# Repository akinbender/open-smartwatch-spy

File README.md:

# Open-Smartwatch Spy Edition beta
Based on the open source smartwatch project [Open-Smartwatch](https://open-smartwatch.github.io/) by [Paul's 3D Things](https://www.instagram.com/pauls_3d_things/?hl=en).
The rugged box is designed after this thingiverse [project](https://www.thingiverse.com/thing:4094861)
Check out my twitter [thread](https://twitter.com/AlternatifAkin/status/1460656525509369863) about the build.

## Must TODOs for v1.0 release
1. Fix button placements. (Buttons are in wrong order)
2. add female connector for battery, soldering is really unpleasent at that point of the assembly.
3. buy some other micro stepper motor such as [this geared one](https://www.ebay.de/itm/193621782182?_trkparms=amclksrc%3DITM%26aid%3D111001%26algo%3DREC.SEED%26ao%3D1%26asc%3D20170511121231%26meid%3D0d5549f075dd4680823e29a32ba356f4%26pid%3D100675%26rk%3D8%26rkt%3D15%26sd%3D114305088477%26itm%3D193621782182%26pmt%3D1%26noa%3D1%26pg%3D2380057%26brand%3DUnbranded&_trksid=p2380057.c100675.m4236&_trkparms=pageci%3A7b14f08c-a37a-11ec-b54c-b2d4c27de75e%7Cparentrq%3A87caf1d717f0ab9e8780c580fffe10da%7Ciid%3A1) and a female [connector](https://www.aliexpress.com/item/4000012574440.html?spm=a2g0o.productlist.0.0.6e081f6dXTVHuh&algo_pvid=905ba21a-fd4a-4362-94af-929b954b7658&algo_exp_id=905ba21a-fd4a-4362-94af-929b954b7658-18&pdp_ext_f=%7B%22sku_id%22%3A%2210000000031868706%22%7D&pdp_pi=-1%3B1.22%3B-1%3B-1%40salePrice%3BEUR%3Bsearch-mainSearch) for it.
4. find schematic and footprint of the afformentioned female connector for the board, and order new pcb.
5. 3d design of the new motor & release mechanism
6. finish osw firmware extension for motor control (didn't check it in, not required at this point)
7. Fix rugged box design. (Current design cannot fit the straps and only has two dart holders) Also gotta fix my 3d printer to print another one.. 

## Optional TODOs
Check out Paul's instagram page, he has designed an awesome new watch. Ultimately and hopefully, I will also switch to the new board design.  I dont know which changes are going to be included when, but I have some plans.

1. switch micro-USB for [waterproof 4 pin connector](https://www.aliexpress.com/item/1005003687986489.html?spm=a2g0o.productlist.0.0.41f07ac9adyMLZ&algo_pvid=9baeaac9-50b3-4902-a8c2-167efe2e5cce&aem_p4p_detail=20220314132643344794801503300032362813&algo_exp_id=9baeaac9-50b3-4902-a8c2-167efe2e5cce-0&pdp_ext_f=%7B%22sku_id%22%3A%2212000026806960583%22%7D&pdp_pi=-1%3B8.4%3B-1%3B6.29%40salePrice%3BEUR%3Bsearch-mainSearch)
2. switch buttons for some waterproof alternative, maybe seperate pcb touch buttons?
3. waterproof design with O-rings and stuff, don't really know how yet..
4. Induction Charging [option](https://www.aliexpress.com/item/1005003691851748.html?spm=a2g0o.productlist.0.0.fb831482BUJV1L&algo_pvid=5ddf7b3c-2e64-4216-bba5-416096ba6f9b&aem_p4p_detail=202203141410075793754545811920016464366&algo_exp_id=5ddf7b3c-2e64-4216-bba5-416096ba6f9b-0&pdp_ext_f=%7B%22sku_id%22%3A%2212000026821101659%22%7D&pdp_pi=-1%3B14.19%3B-1%3B1.81%40salePrice%3BEUR%3Bsearch-mainSearch) 

## Notes
Currently there is a fully plastic test dart, and one that can be fashioned out of a M3 allen key. Depending on multiple build desicions, you can really end up hurting someone with the metal dart. This should go without saying, but I (and Paul) obviously do not accept any responsibility, I never do..

Also going to visit a local magic shop for guidance about trick darts. Magic is all about deception, most spygear too.. So maybe I might build some pyro, flash or smoke darts. Can also build an injector dart. I looked closely to my Covid vaccine injector, it can fit inside the chamber but there is no way that it can be useful.

###### I named the project because well, it's obvious right? But my aim was to build a self protection gear in the form of a daily wearable item for my sis and my mom. And lets face it, shooting darts is not the optimal solution for them. Long story short, after v1.0 release an alternative design with a gas canister instead of a dart shooter is also needed.

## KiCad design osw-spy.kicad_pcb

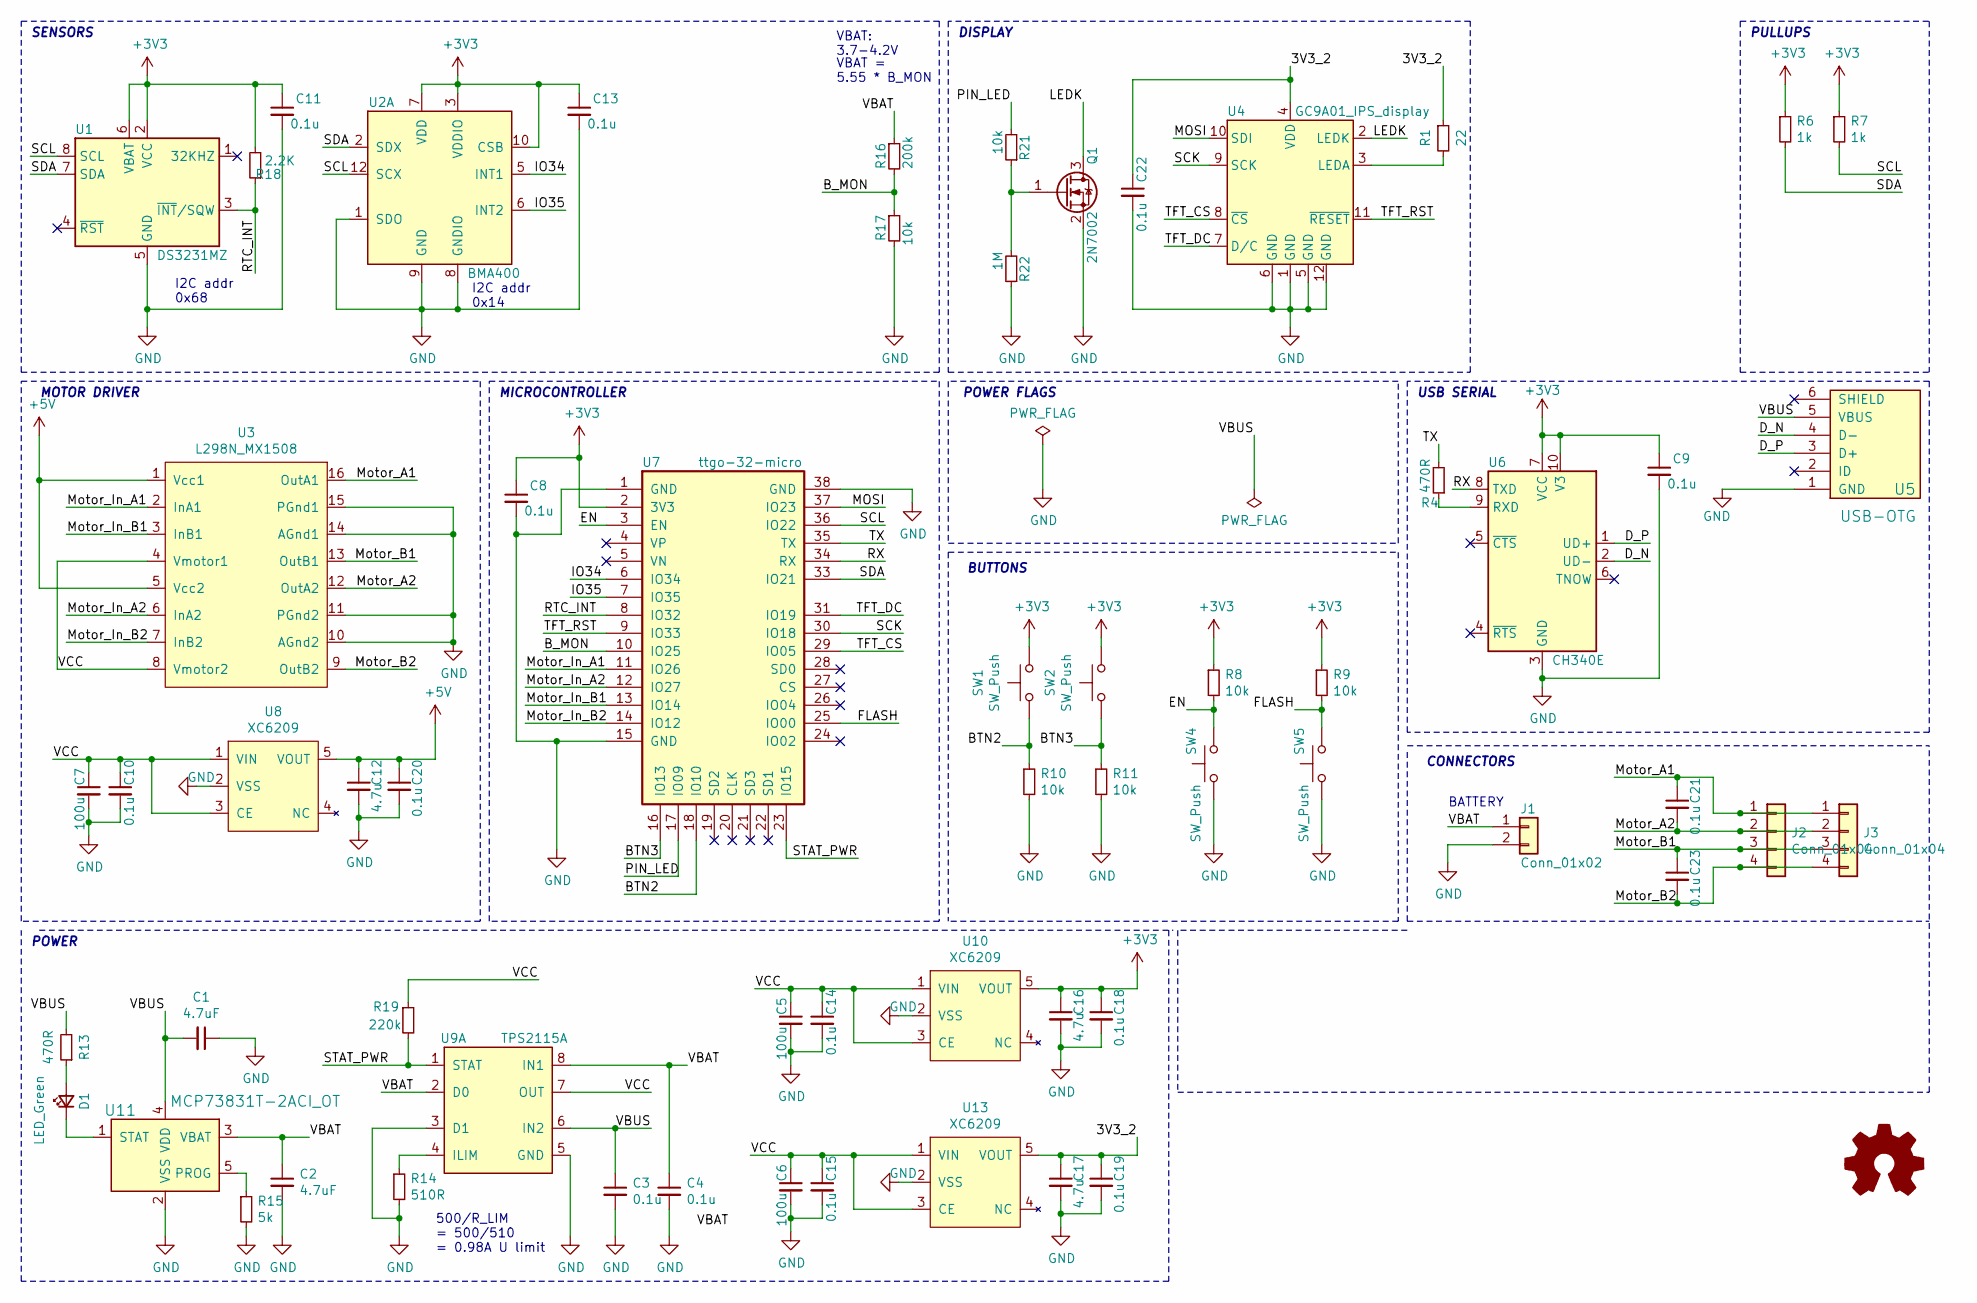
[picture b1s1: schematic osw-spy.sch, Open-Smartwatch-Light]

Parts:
C1, C2: 4.7uF; C_0603_1608Metric
C3, C4, C8, C9, C10, C11, C13, C14, C15, C18, C19, C20, C21, C22, C23: 0.1u; C_0603_1608Metric
C5, C6, C7: 100u; C_1206_3216Metric
C12, C16, C17: 4.7u; C_0603_1608Metric
D1: LED_Green; LED_0805_2012Metric
J1: Conn_01x02; PinHeader_1x02_P2.54mm_Vertical
J2, J3: Conn_01x04; PinHeader_1x04_P2.54mm_Vertical
Q1: 2N7002; SOT-23
R1: 22; R_0603_1608Metric
R4, R13: 470R; R_0603_1608Metric
R6, R7: 1k; R_0603_1608Metric
R8, R9, R10, R11, R17, R21: 10k; R_0603_1608Metric
R14: 510R; R_0603_1608Metric
R15: 5k; R_0603_1608Metric
R16: 200k; R_0603_1608Metric
R18: 2.2K; R_0603_1608Metric
R19: 220k; R_0603_1608Metric
R22: 1M; R_0603_1608Metric
SW1, SW2, SW4, SW5: SW_Push; button_side_smd
U1: DS3231MZ; SOIC-8_3.9x4.9mm_P1.27mm
U2: BMA400; LGA-12_2x2mm_P0.5mm; MPN BMA400; DigiKey_PN 828-1081-1-ND
U3: L298N_MX1508; SOP-16_3.9x9.9mm_P1.27mm
U4: GC9A01_IPS_display
U5: USB-OTG; USBmicro-B
U6: CH340E; MSOP-10_3x3mm_P0.5mm
U7: ttgo-32-micro
U8, U10, U13: XC6209; SOT-23-5
U9: TPS2115A; TSSOP-8_4.4x3mm_P0.65mm; MPN TPS2115APWR; DigiKey_PN 296-16940-1-ND
U11: MCP73831T-2ACI_OT; SOT-23-5; MPN MCP73831T-2ACI/OT; Digi-Key_PN MCP73831T-2ACI/OTCT-ND

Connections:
+3V3: C8.1, C9.1, C11.1, C13.1, C16.1, C18.1, R6.1, R7.1, R8.1, R9.1, R18.2, SW1.2, SW2.2, U1.2 (VCC), U1.6 (VBAT), U2.3 (VDDIO), U2.7 (VDD), U2.10 (CSB), U6.7 (VCC), U6.10 (V3), U7.2 (3V3), U10.5 (VOUT)
+5V: C12.1, C20.1, U3.1 (Vcc1), U3.5 (Vcc2), U8.5 (VOUT)
/3V3_2: C17.1, C19.1, C22.1, R1.1, U4.4 (VDD), U13.5 (VOUT)
/BTN2: R10.1, SW1.1, U7.18 (IO10)
/BTN3: R11.1, SW2.1, U7.16 (IO13)
/B_MON: R16.2, R17.1, U7.10 (IO25)
/D_N: U5.4 (D-), U6.2 (UD-)
/D_P: U5.3 (D+), U6.1 (UD+)
/EN: R8.2, SW4.2, U7.3 (EN)
/FLASH: R9.2, SW5.2, U7.25 (IO00)
/IO34: U2.5 (INT1), U7.6 (IO34)
/IO35: U2.6 (INT2), U7.7 (IO35)
/LEDK: Q1.3 (D), U4.2 (LEDK)
/MOSI: U4.10 (SDI), U7.37 (IO23)
/Motor_A1: C21.1, J2.1, J3.1, U3.16 (OutA1)
/Motor_A2: C21.2, J2.2, J3.2, U3.12 (OutA2)
/Motor_B1: C23.1, J2.3, J3.3, U3.13 (OutB1)
/Motor_B2: C23.2, J2.4, J3.4, U3.9 (OutB2)
/Motor_In_A1: U3.2 (InA1), U7.11 (IO26)
/Motor_In_A2: U3.6 (InA2), U7.12 (IO27)
/Motor_In_B1: U3.3 (InB1), U7.13 (IO14)
/Motor_In_B2: U3.7 (InB2), U7.14 (IO12)
/PIN_LED: R21.2, U7.17 (IO09)
/RTC_INT: R18.1, U1.3 (~INT~/SQW), U7.8 (IO32)
/RX: U6.8 (TXD), U7.34 (RX)
/SCK: U4.9 (SCK), U7.30 (IO18)
/SCL: R7.2, U1.8 (SCL), U2.12 (SCX), U7.36 (IO22)
/SDA: R6.2, U1.7 (SDA), U2.2 (SDX), U7.33 (IO21)
/STAT_PWR: R19.2, U7.23 (IO15), U9.1 (STAT)
/TFT_CS: U4.8 (~CS), U7.29 (IO05)
/TFT_DC: U4.7 (D/C), U7.31 (IO19)
/TFT_RST: U4.11 (~RESET), U7.9 (IO33)
/TX: R4.2, U7.35 (TX)
/VBAT: C2.1, C4.1, J1.1, R16.1, U9.2 (D0), U9.8 (IN1), U11.3 (VBAT)
/VBUS: C1.2, C3.1, R13.2, U5.5 (VBUS), U9.6 (IN2), U11.4 (VDD)
/VCC: C5.1, C6.1, C7.1, C10.1, C14.1, C15.1, R19.1, U3.4 (Vmotor1), U3.8 (Vmotor2), U8.1 (VIN), U8.3 (CE), U9.7 (OUT), U10.1 (VIN), U10.3 (CE), U13.1 (VIN), U13.3 (CE)
GND: C1.1, C2.2, C3.2, C4.2, C5.2, C6.2, C7.2, C8.2, C9.2, C10.2, C11.2, C12.2, C13.2, C14.2, C15.2, C16.2, C17.2, C18.2, C19.2, C20.2, C22.2, J1.2, Q1.2 (S), R10.2, R11.2, R14.2, R15.2, R17.2, R22.1, SW4.1, SW5.1, U1.5 (GND), U2.1 (SDO), U2.8 (GNDIO), U2.9 (GND), U3.10 (AGnd2), U3.11 (PGnd2), U3.14 (AGnd1), U3.15 (PGnd1), U4.1 (GND), U4.5 (GND), U4.6 (GND), U4.12 (GND), U5.1 (GND), U6.3 (GND), U7.1 (GND), U7.15 (GND), U7.38 (GND), U8.2 (VSS), U9.3 (D1), U9.5 (GND), U10.2 (VSS), U11.2 (VSS), U13.2 (VSS)
unnamed: D1.1 (K), U11.1 (STAT)
unnamed: D1.2 (A), R13.1
unnamed: Q1.1 (G), R21.1, R22.2
unnamed: R1.2, U4.3 (LEDA)
unnamed: R4.1, U6.9 (RXD)
unnamed: R14.1, U9.4 (ILIM)
unnamed: R15.1, U11.5 (PROG)

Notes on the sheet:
500/R_LIM = 500/510 = 0.98A U limit
SENSORS
POWER
DISPLAY
USB SERIAL
BUTTONS
PULLUPS
BATTERY
VBAT: 3.7-4.2V
VBAT = 5.55 * B_MON
MICROCONTROLLER
POWER FLAGS
I2C addr 0x68
I2C addr 0x14
CONNECTORS
MOTOR DRIVER

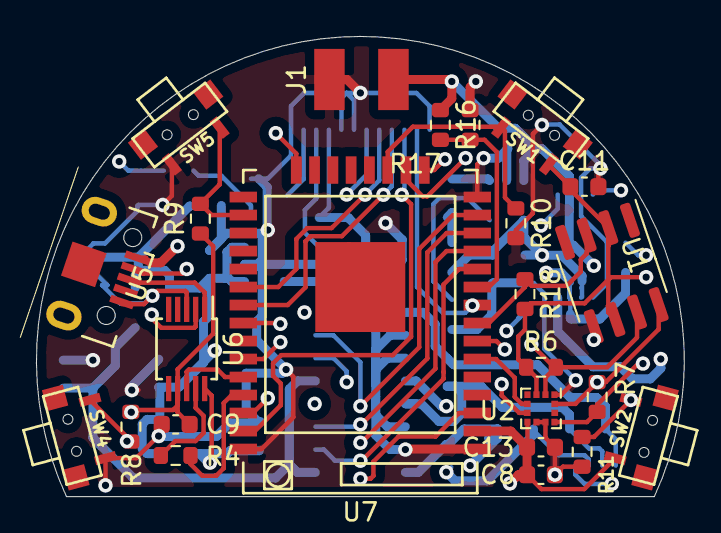
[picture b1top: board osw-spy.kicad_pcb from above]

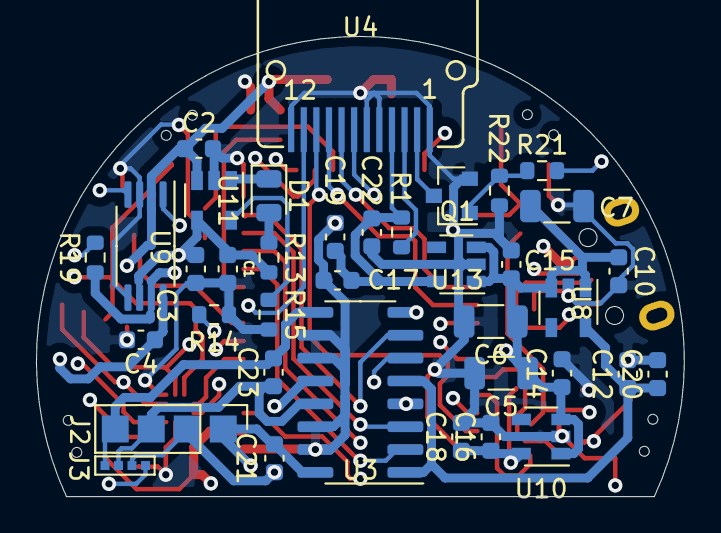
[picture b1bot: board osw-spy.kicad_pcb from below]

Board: 4 copper layers, 36.0 x 25.6 mm, 61 parts (37 on the bottom side), 44 nets.
